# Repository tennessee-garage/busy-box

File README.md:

# busy-box
A collection of controls and displays with supporting PCB layouts and code such that they can be dropped into different applications.

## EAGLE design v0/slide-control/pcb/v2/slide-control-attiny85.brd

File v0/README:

This directory contains inital development for these controls with various development environments and various PCB editors.  It is useful to keep around while developing v1 using consistenti development tooling (vscode) and layout tooling (kicad)

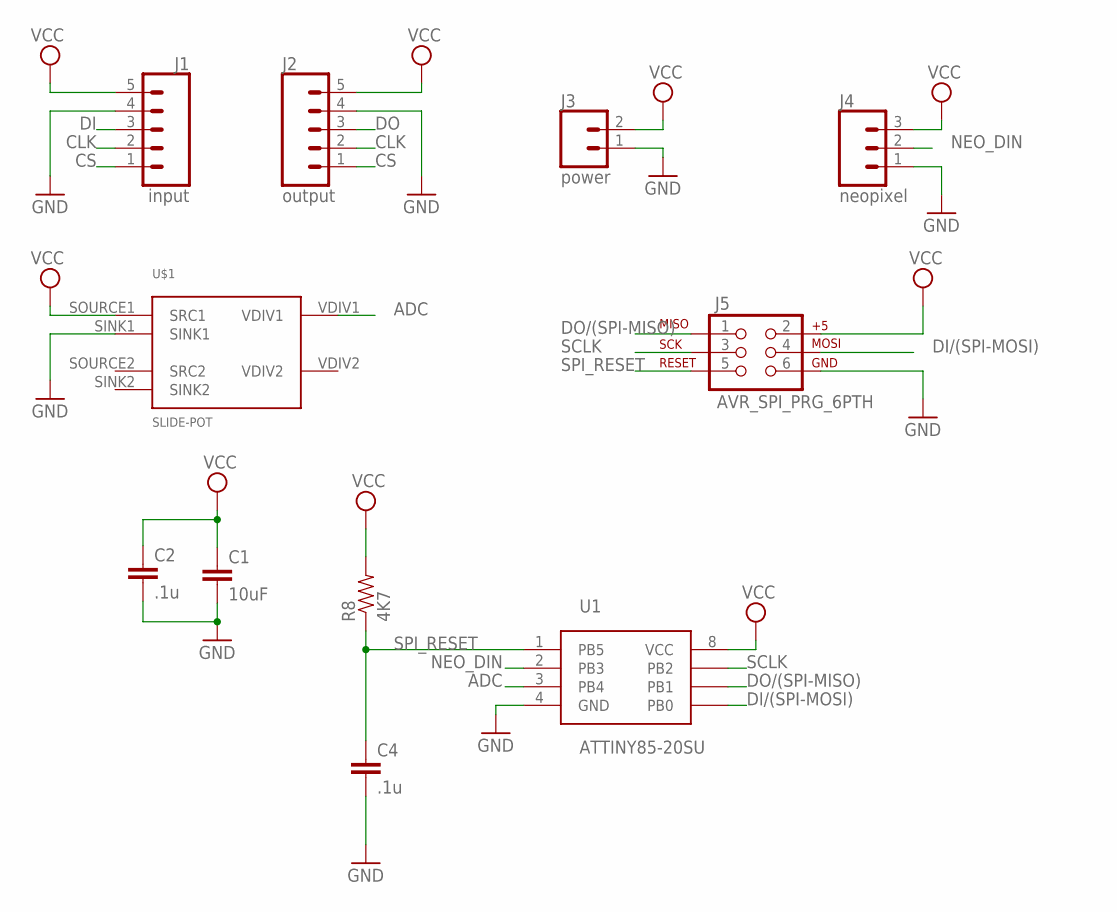
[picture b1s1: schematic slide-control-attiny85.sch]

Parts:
C1: 10uF; 1206
C2, C4: .1u; 0805
J1: input; 1X05
J2: output; 1X05
J3: power; 1X02
J4: neopixel; 1X03
J5: AVR_SPI_PRG_6PTH; 2X3
R8: 4K7; 0805
U1: ATTINY85-20SU; SOIC-8
U$1: SLIDE-POT

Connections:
ADC: U1.3 (PB4), U$1.VDIV1
CLK: J1.2, J2.2
CS: J1.1, J2.1
DI: J1.3
DI/(SPI-MOSI): J5.4, U1.5 (PB0)
DO: J2.3
DO/(SPI-MISO): J5.1, U1.6 (PB1)
GND: C1.2, C2.2, C4.2, J1.4, J2.4, J3.1, J4.1, J5.6, U1.4 (GND), U$1.SINK1
NEO_DIN: J4.2, U1.2 (PB3)
SCLK: J5.3, U1.7 (PB2)
SPI_RESET: C4.1, J5.5, R8.1, U1.1 (PB5)
VCC: C1.1, C2.1, J1.5, J2.5, J3.2, J4.3, J5.2, R8.2, U1.8 (VCC), U$1.SOURCE1 (SRC1)

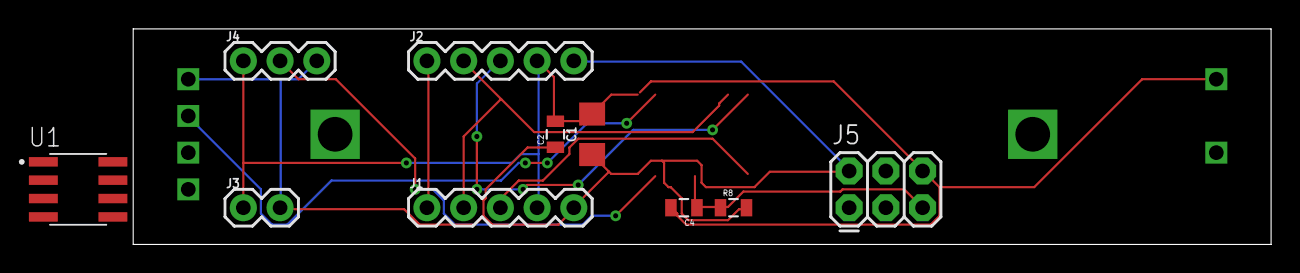
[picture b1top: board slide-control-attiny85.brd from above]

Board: 2 copper layers, 78.7 x 14.9 mm, 11 parts (1 on the bottom side), 10 nets.

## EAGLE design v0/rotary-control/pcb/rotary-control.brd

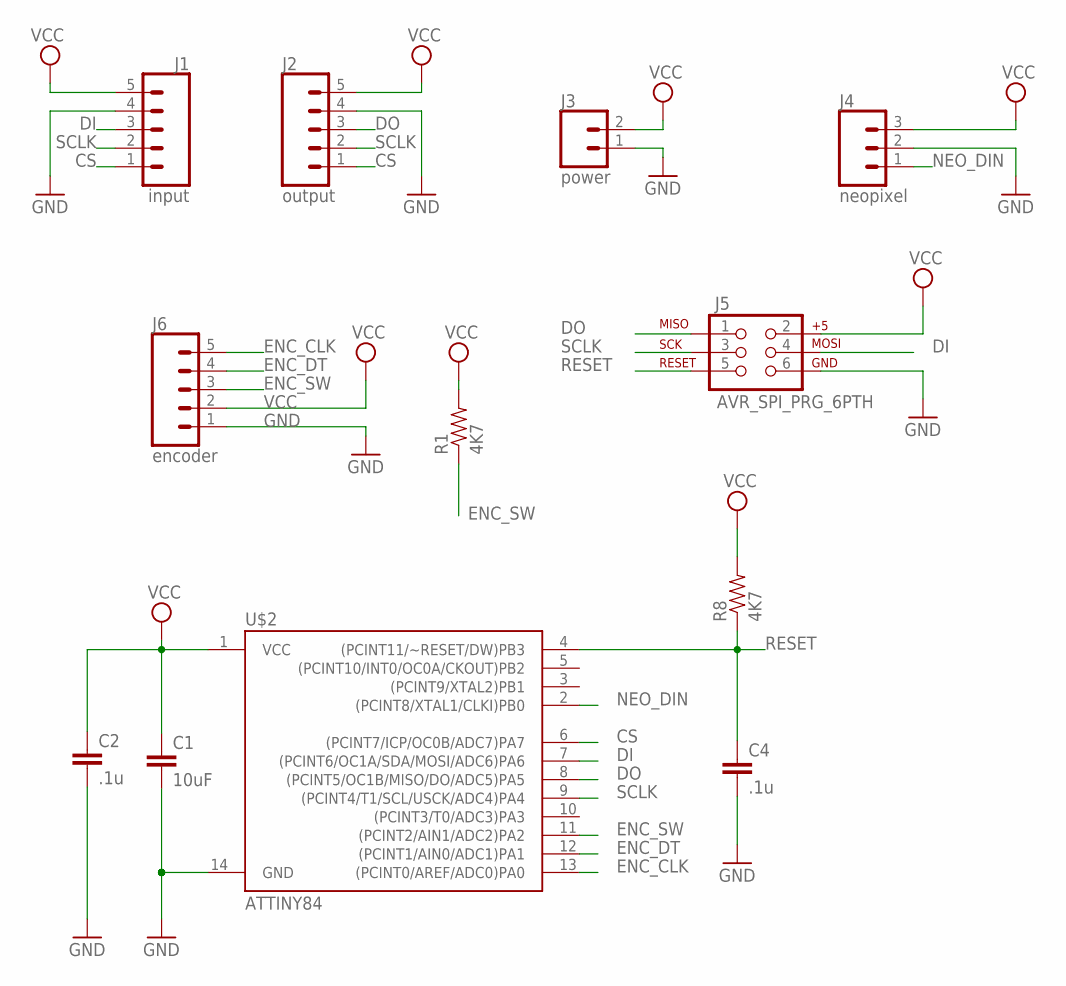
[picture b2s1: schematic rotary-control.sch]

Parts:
C1: 10uF; 1206
C2, C4: .1u; 0805
J1: input; 1X05
J2: output; 1X05
J3: power; 1X02
J4: neopixel; 1X03
J5: AVR_SPI_PRG_6PTH; 2X3
J6: encoder; 1X05
R1, R8: 4K7; 0805
U$2: ATTINY84; SO14

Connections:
CS: J1.1, J2.1, U$2.6 ((PCINT7/ICP/OC0B/ADC7)PA7)
DI: J1.3, J5.4, U$2.7 ((PCINT6/OC1A/SDA/MOSI/ADC6)PA6)
DO: J2.3, J5.1, U$2.8 ((PCINT5/OC1B/MISO/DO/ADC5)PA5)
ENC_CLK: J6.5, U$2.13 ((PCINT0/AREF/ADC0)PA0)
ENC_DT: J6.4, U$2.12 ((PCINT1/AIN0/ADC1)PA1)
ENC_SW: J6.3, R1.1, U$2.11 ((PCINT2/AIN1/ADC2)PA2)
GND: C1.2, C2.2, C4.2, J1.4, J2.4, J3.1, J4.2, J5.6, J6.1, U$2.14 (GND)
NEO_DIN: J4.1, U$2.2 ((PCINT8/XTAL1/CLKI)PB0)
RESET: C4.1, J5.5, R8.1, U$2.4 ((PCINT11/~RESET/DW)PB3)
SCLK: J1.2, J2.2, J5.3, U$2.9 ((PCINT4/T1/SCL/USCK/ADC4)PA4)
VCC: C1.1, C2.1, J1.5, J2.5, J3.2, J4.3, J5.2, J6.2, R1.2, R8.2, U$2.1 (VCC)

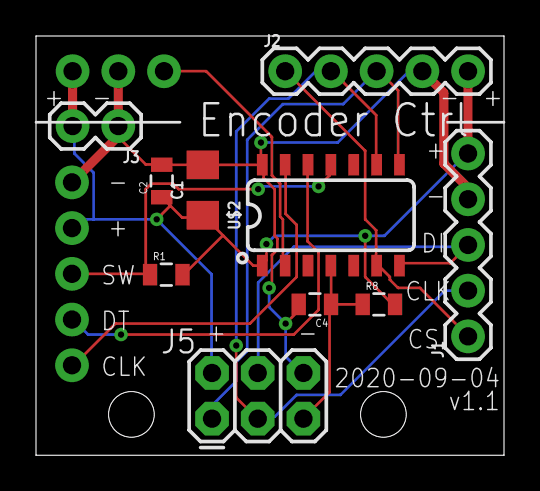
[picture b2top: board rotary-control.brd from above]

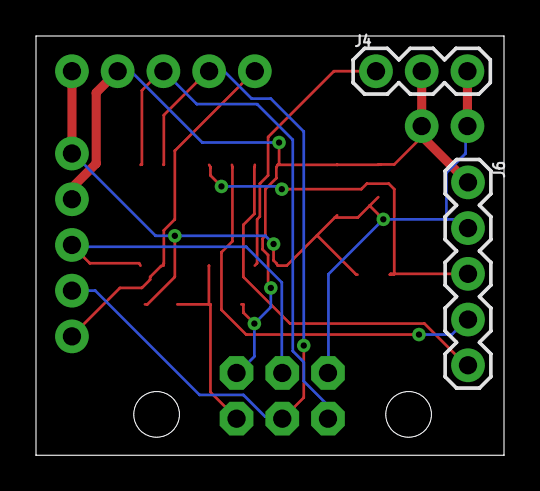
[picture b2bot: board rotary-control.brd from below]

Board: 2 copper layers, 26.0 x 23.3 mm, 12 parts (2 on the bottom side), 11 nets.

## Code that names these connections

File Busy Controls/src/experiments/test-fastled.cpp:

#include <Arduino.h>
#include <FastLED.h>

#define DEMO_PIN_CLOBBER true

#define NEO_PIN 10
//#define NEO_PIN PIN_PB0
#define NUM_LEDS 12

#define CLK_PIN PIN_PA0
#define DT_PIN PIN_PA1
#define BUTTON_PIN PIN_PA2

CRGB leds[NUM_LEDS];

void clearLeds() {
    for (int i=0; i < NUM_LEDS; i++) {
        leds[i] = CRGB::Black;
    }
    FastLED.show();
}

void cycleLeds() {
    uint8_t hue = 0;
    uint8_t sat = 255;
    uint8_t val = 255;

    for (int i=0; i < NUM_LEDS; i++) {
        leds[i] = CHSV(hue, sat, val);
        hue += (int) 255.0/NUM_LEDS;
        
        FastLED.show();
        delay(500);
    }
}

void setup() {
    if (DEMO_PIN_CLOBBER) {
        pinMode(CLK_PIN, INPUT);
        pinMode(DT_PIN, INPUT);
        pinMode(BUTTON_PIN, INPUT);

        // Set the pullup resistor on the button pin
        digitalWrite(BUTTON_PIN, HIGH);

        FastLED.addLeds<WS2812B, NEO_PIN, GRB>(leds, NUM_LEDS).setCorrection( TypicalSMD5050 );
    } else {
        FastLED.addLeds<WS2812B, NEO_PIN, GRB>(leds, NUM_LEDS).setCorrection( TypicalSMD5050 );
        pinMode(CLK_PIN, INPUT);
    }
}

void loop() {
    clearLeds();
    cycleLeds();
}

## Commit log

2024-06-26 Initial commit with original code and designs
2024-06-26 New version of PCB and code.
    Standardizing on Visual Studio Code for development and Kicad for layout.
2024-06-27 Fixed encoder count handling
    * CCW wasn't working due to integer underflow
    * a few things needed to be set to intX_t vs uintX_t to allow for negative numbers that would later be cast to integer
    * adjusted behavior to lock low/high boundaries (e.g. no wrap around in either direction)
2024-06-27 Added new RingLED class to encapsulate all the neopixel ring handling
2024-06-28 Big simplification to the platformio.ini file, splitting out common parameters into the generic [env] section. Also created production versions of the seven segment and vu controls, from the test fil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
2024-06-28 Make sure we disable SPI on devices that are not selected. This didn't matter for read only devices, but for controls that send back a value, this is important. All devices on the SPI line will send 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
2024-06-28 Adding some comments to the libraries to describe what they do at a high level.
2024-06-28 Make it so poll() returns T/F depending on whether a new value was read from the encoder.
2024-06-28 Make sure there's a default display method set.
2024-06-28 Control the SPI bus more tighly Make sure the DO line is set to INPUT when not selected so it floats and doesn't clobber other devices. Also break out the functionality into methods so that private d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
2024-06-28 Add a test pattern to startup
2024-06-28 Checkpoint sending values back to the host. Still TBD: sending button presses, receiving commands to switch the display
2024-06-28 Add control over LEDs, and a test pattern Also of note, added an ease method to allow the needle to drift to zero vs slamming down.
2024-07-10 Fixed SPI functionality for 3+ client devices. This included removing the interrupt functionality, as that was creating too many timing issues. Additionally, the DO line is pulsed as a way to alert t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
2024-07-10 All three existing controls now working with intended features in test mode This includes sending button presses out from the rotary control and the VU meter taking commands to set LEDs.
2024-07-10 Checkpointing some experiment scripts.
2024-07-24 Allow external control of some aspects of the rotary control

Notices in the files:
parts and their libraries:
SparkFun-Capacitors: Licensing: Creative Commons ShareAlike 4.0 International - https://creativecommons.org/licenses/by-sa/4.0
SparkFun-Connectors: Licensing: CC v3.0 Share-Alike You are welcome to use this library for commercial purposes.
